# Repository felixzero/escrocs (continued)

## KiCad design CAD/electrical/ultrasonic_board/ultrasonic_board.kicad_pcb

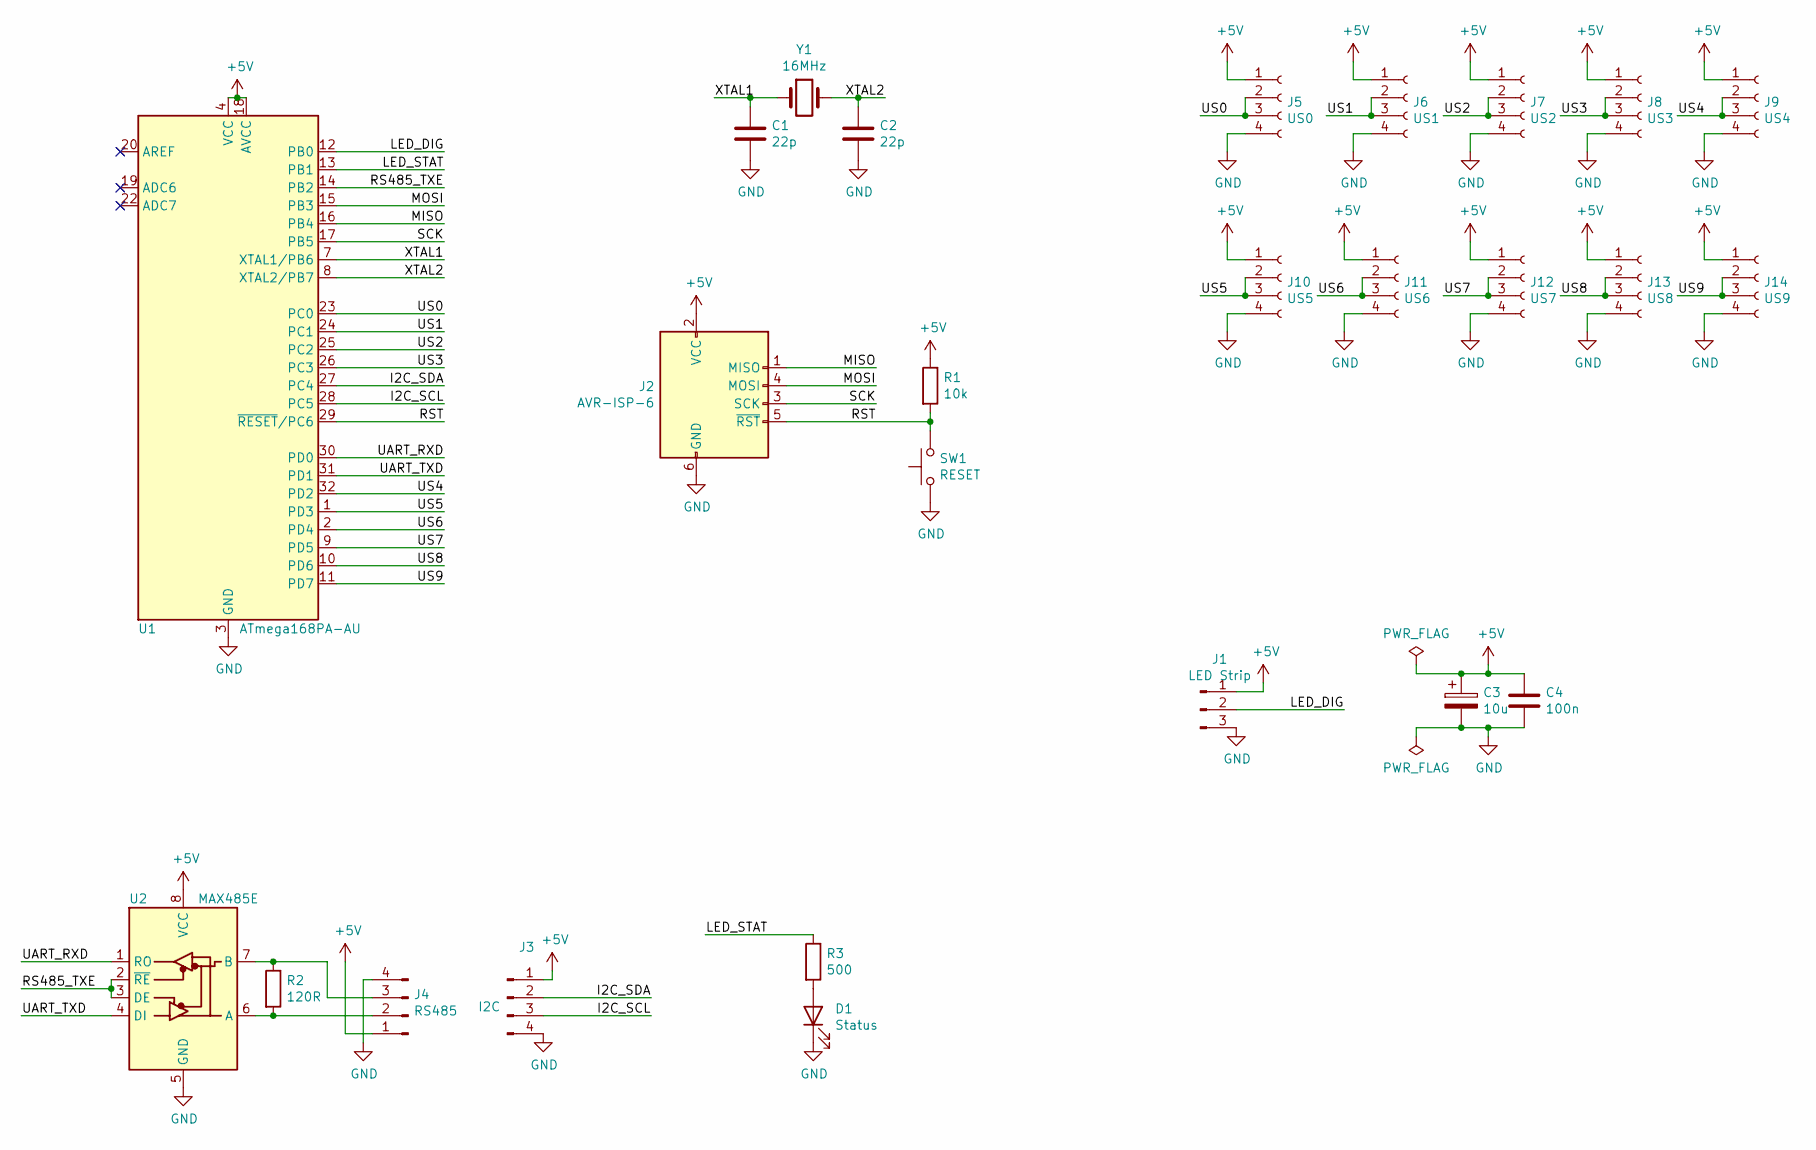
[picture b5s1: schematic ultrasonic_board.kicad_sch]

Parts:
C1, C2: 22p; C_0603_1608Metric
C3: 10u; CP_Radial_D8.0mm_P3.80mm
C4: 100n; C_0603_1608Metric
D1: Status; LED_0805_2012Metric
J1: LED Strip; Molex_KK-254_AE-6410-03A_1x03_P2.54mm_Vertical
J2: AVR-ISP-6; PinHeader_2x03_P2.54mm_Vertical
J3: I2C; Molex_KK-254_AE-6410-04A_1x04_P2.54mm_Vertical
J4: RS485; Molex_KK-254_AE-6410-04A_1x04_P2.54mm_Vertical
J5: US0; PinSocket_1x04_P2.54mm_Vertical
J6: US1; PinSocket_1x04_P2.54mm_Vertical
J7: US2; PinSocket_1x04_P2.54mm_Vertical
J8: US3; PinSocket_1x04_P2.54mm_Vertical
J9: US4; PinSocket_1x04_P2.54mm_Vertical
J10: US5; PinSocket_1x04_P2.54mm_Vertical
J11: US6; PinSocket_1x04_P2.54mm_Vertical
J12: US7; PinSocket_1x04_P2.54mm_Vertical
J13: US8; PinSocket_1x04_P2.54mm_Vertical
J14: US9; PinSocket_1x04_P2.54mm_Vertical
R1: 10k; R_0603_1608Metric
R2: 120R; R_0603_1608Metric
R3: 500; R_0603_1608Metric
SW1: RESET; SW_PUSH_6mm
U1: ATmega168PA-AU; TQFP-32_7x7mm_P0.8mm
U2: MAX485E; SOIC-8_3.9x4.9mm_P1.27mm
Y1: 16MHz; Crystal_SMD_HC49-SD

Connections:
+5V: C3.1, C4.1, J1.1, J2.2 (VCC), J3.1, J4.1, J5.1, J6.1, J7.1, J8.1, J9.1, J10.1, J11.1, J12.1, J13.1, J14.1, R1.1, U1.4 (VCC), U1.6 (VCC), U1.18 (AVCC), U2.8 (VCC)
/I2C_SCL: J3.3, U1.28 (PC5)
/I2C_SDA: J3.2, U1.27 (PC4)
/LED_DIG: J1.2, U1.12 (PB0)
/LED_STAT: R3.1, U1.13 (PB1)
/MISO: J2.1 (MISO), U1.16 (PB4)
/MOSI: J2.4 (MOSI), U1.15 (PB3)
/RS485_TXE: U1.14 (PB2), U2.2 (~RE), U2.3 (DE)
/RST: J2.5 (~RST), R1.2, SW1.2, U1.29 (~RESET/PC6)
/SCK: J2.3 (SCK), U1.17 (PB5)
/UART_RXD: U1.30 (PD0), U2.1 (RO)
/UART_TXD: U1.31 (PD1), U2.4 (DI)
/US0: J5.2, J5.3, U1.23 (PC0)
/US1: J6.2, J6.3, U1.24 (PC1)
/US2: J7.2, J7.3, U1.25 (PC2)
/US3: J8.2, J8.3, U1.26 (PC3)
/US4: J9.2, J9.3, U1.32 (PD2)
/US5: J10.2, J10.3, U1.1 (PD3)
/US6: J11.2, J11.3, U1.2 (PD4)
/US7: J12.2, J12.3, U1.9 (PD5)
/US8: J13.2, J13.3, U1.10 (PD6)
/US9: J14.2, J14.3, U1.11 (PD7)
/XTAL1: C1.1, U1.7 (XTAL1/PB6), Y1.1
/XTAL2: C2.1, U1.8 (XTAL2/PB7), Y1.2
GND: C1.2, C2.2, C3.2, C4.2, D1.1 (K), J1.3, J2.6 (GND), J3.4, J4.4, J5.4, J6.4, J7.4, J8.4, J9.4, J10.4, J11.4, J12.4, J13.4, J14.4, SW1.1, U1.3 (GND), U1.5 (GND), U1.21 (GND), U2.5 (GND)
unnamed: D1.2 (A), R3.2
unnamed: J4.2, R2.2, U2.6 (A)
unnamed: J4.3, R2.1, U2.7 (B)

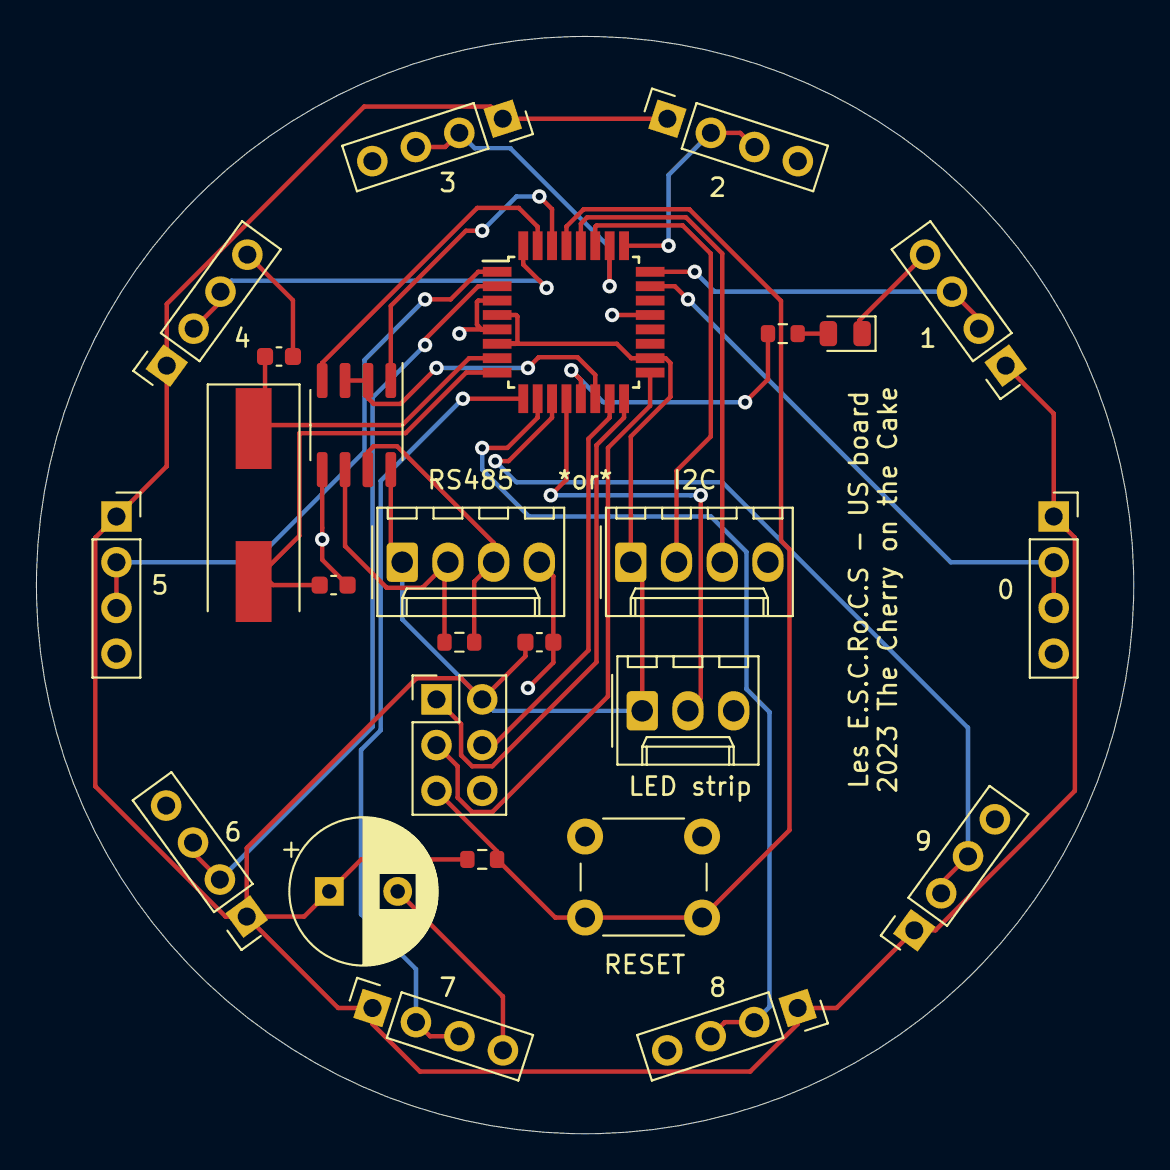
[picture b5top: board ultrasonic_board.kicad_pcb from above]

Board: 2 copper layers, 61.0 x 61.0 mm, 26 parts (0 on the bottom side), 28 nets.

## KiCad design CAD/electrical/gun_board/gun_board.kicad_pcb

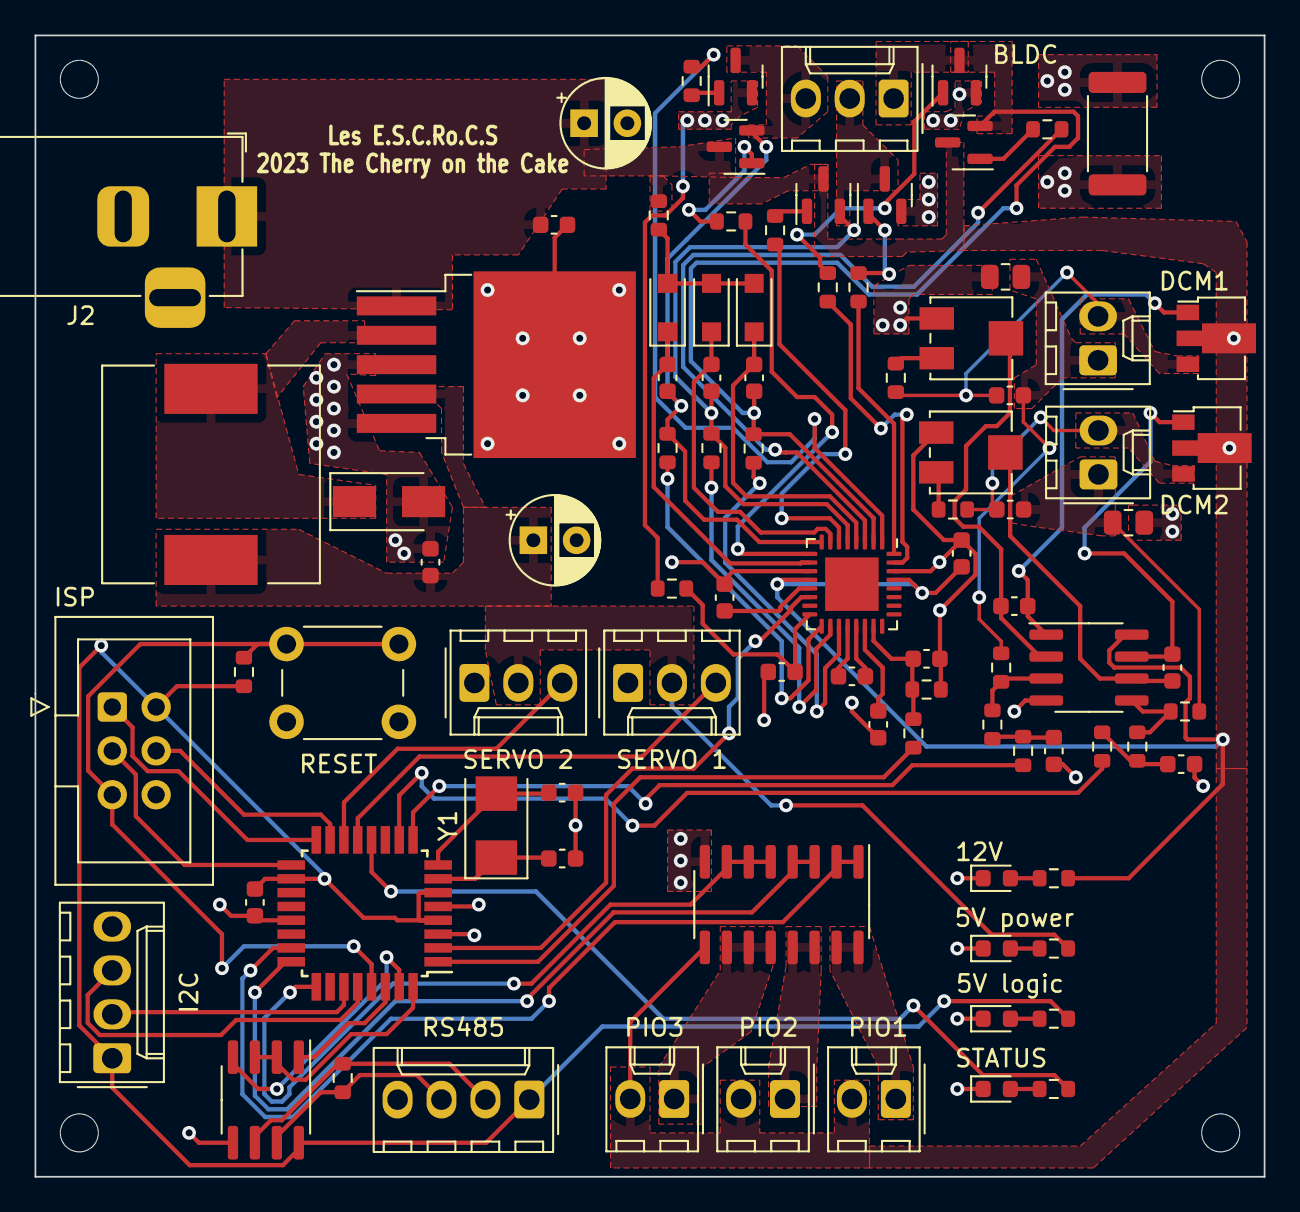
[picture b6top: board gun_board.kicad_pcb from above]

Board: 2 copper layers, 71.1 x 66.0 mm, 91 parts (0 on the bottom side), 78 nets.

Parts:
5V logic, 5V power, 12V: LED; LED_0603_1608Metric
BLDC: BLDC; Molex_KK-254_AE-6410-03A_1x03_P2.54mm_Vertical
C1, C3: 22p; C_0603_1608Metric
C2, C5, C7, C8, C11, C14, C16, C18, C19, C20, C21, C22: 100n; C_0603_1608Metric
C4: 47u; CP_Radial_D5.0mm_P2.50mm
C6: 10u; CP_Radial_D5.0mm_P2.50mm
C9, C10, C12, C13: 22n; C_0603_1608Metric
C15, C17: 100p; C_0603_1608Metric
D1: SS54; D_SMA
D6, D7, D8: D; D_SOD-123F
DCM1: DC Motor 1; Molex_KK-254_AE-6410-02A_1x02_P2.54mm_Vertical
DCM2: DC Motor 2; Molex_KK-254_AE-6410-02A_1x02_P2.54mm_Vertical
I2C: I2C; Molex_KK-254_AE-6410-04A_1x04_P2.54mm_Vertical
ISP: AVR-ISP-6; IDC-Header_2x03_P2.54mm_Vertical
J2: Barrel_Jack; BarrelJack_Horizontal
L2: 100u; L_12x12mm_H6mm
PIO1: HPIO 1; Molex_KK-254_AE-6410-02A_1x02_P2.54mm_Vertical
PIO2: HPIO 2; Molex_KK-254_AE-6410-02A_1x02_P2.54mm_Vertical
PIO3: HPIO 3; Molex_KK-254_AE-6410-02A_1x02_P2.54mm_Vertical
Q1, Q2: C9634; SOT-89-3
Q3, Q4, Q5, Q6, Q7, Q8: AO3400A; SOT-23
R1: 470R; R_0603_1608Metric
R2, R4, R5: 100R; R_0603_1608Metric
R3: 120R; R_0603_1608Metric
R6, R7, R8, R9, R10, R12, R13, R14, R15, R17, R19: 10k; R_0603_1608Metric
R11, R16: 1R; R_0805_2012Metric
R18: 100k; R_0603_1608Metric
R20: 10R; R_0603_1608Metric
R21, R22, R23, R24, R25, R26: 47R; R_0603_1608Metric
R27: 60mR; R_2512_6332Metric
R28, R29, R30: 33k; R_0603_1608Metric
RESET: RESET; SW_PUSH_6mm
RS485: RS485; Molex_KK-254_AE-6410-04A_1x04_P2.54mm_Vertical
RV1, RV2: 1k; Potentiometer_Bourns_3314J_Vertical
SERVO 1: Servo 1; Molex_KK-254_AE-6410-03A_1x03_P2.54mm_Vertical
SERVO 2: Servo 2; Molex_KK-254_AE-6410-03A_1x03_P2.54mm_Vertical
STATUS: LED; LED_0603_1608Metric
U1: LM2576HVS-5; TO-263-5_TabPin3
U2: ATmega328P-A; TQFP-32_7x7mm_P0.8mm
U3: MAX485E; SOIC-8_3.9x4.9mm_P1.27mm
U4: LM2904; SOIC-8_3.9x4.9mm_P1.27mm
U5: ULN2003; SOIC-16_3.9x9.9mm_P1.27mm
U6: PT2522; QFN-32-1EP_5x5mm_P0.5mm_EP3.1x3.1mm
Y1: Crystal; Crystal_SMD_5032-2Pin_5.0x3.2mm

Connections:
+5V: C2.1, I2C.1, ISP.2 (VCC), R4.1, R6.1, RS485.1, U2.4 (VCC), U2.6 (VCC), U2.18 (AVCC), U3.8 (VCC)
+5VP: C6.1, C7.1, L2.2, R2.1, SERVO 1.2, SERVO 2.2, U1.4 (FB)
+12V: C4.1, C5.1, C18.1, J2.1, PIO1.2, PIO2.2, PIO3.2, Q1.2 (C), Q2.2 (C), Q3.3 (D), Q5.3 (D), Q7.3 (D), R1.1, R20.1, U1.1 (VIN), U4.8 (V+), U5.9 (COM), U6.12 (VDD), U6.29 (VCC)
/BLDC driver/UO: BLDC.3, C20.2, Q3.2 (S), Q4.3 (D), R28.1, U6.8 (VS1)
/BLDC driver/VO: BLDC.2, C21.2, Q5.2 (S), Q6.3 (D), R29.1, U6.5 (VS2)
/BLDC driver/WO: BLDC.1, C22.2, Q7.2 (S), Q8.3 (D), R30.1, U6.2 (VS3)
/BLDC driver/ZCU: R28.2, U6.17 (ZCU)
/BLDC driver/ZCV: R29.2, U6.18 (ZCV)
/BLDC driver/ZCW: R30.2, U6.19 (ZCW)
/BLDC_FW: U2.2 (PD4), U6.14 (FWR)
/BLDC_PWM: R17.2, U2.1 (PD3)
/DCM1_PWM: R7.1, U2.9 (PD5)
/DCM2_PWM: R12.1, U2.10 (PD6)
/HPIO1: U2.23 (PC0), U5.1 (I1), U5.2 (I2)
/HPIO2: U2.24 (PC1), U5.3 (I3), U5.4 (I4)
/HPIO3: U2.25 (PC2), U5.5 (I5), U5.6 (I6), U5.7 (I7)
/I2C_SCL: I2C.3, U2.28 (PC5)
/I2C_SDA: I2C.2, U2.27 (PC4)
/RS485_TXE: U2.32 (PD2), U3.2 (~RE), U3.3 (DE)
/RST: ISP.5 (~RST), R6.2, RESET.1, U2.29 (~RESET/PC6)
/SERVO1: SERVO 1.3, U2.13 (PB1)
/SERVO2: SERVO 2.3, U2.14 (PB2)
/SPI_MISO: ISP.1 (MISO), U2.16 (PB4)
/SPI_MOSI: ISP.4 (MOSI), U2.15 (PB3)
/SPI_SCK: ISP.3 (SCK), U2.17 (PB5)
/STATUS: R5.1, U2.12 (PB0)
/Tunable DC Motor 1/M+: C10.1, DCM1.2, Q1.3 (E), R10.1
/Tunable DC Motor 1/M-: C10.2, DCM1.1, R9.2, R11.1
/Tunable DC Motor 2/M+: C13.1, DCM2.2, Q2.3 (E), R15.1
/Tunable DC Motor 2/M-: C13.2, DCM2.1, R14.2, R16.1
/UART_RXD: U2.30 (PD0), U3.1 (RO)
/UART_TXD: U2.31 (PD1), U3.4 (DI)
/XTAL1: C1.1, U2.7 (XTAL1/PB6), Y1.1
/XTAL2: C3.1, U2.8 (XTAL2/PB7), Y1.2
GND: 5V logic.1 (K), 5V power.1 (K), 12V.1 (K), C1.2, C2.2, C3.2, C4.2, C5.2, C6.2, C7.2, C8.2, C11.2, C14.2, C15.2, C16.2, C18.2, C19.1, D1.2 (A), I2C.4, ISP.6 (GND), J2.2, R11.2, R16.2, R18.2, R27.2, RESET.2, RS485.4, RV1.1, RV2.1, SERVO 1.1, SERVO 2.1, STATUS.1 (K), U1.3 (GND), U1.5 (~ON/OFF), U2.3 (GND), U2.5 (GND), U2.21 (GND), U3.5 (GND), U4.4 (V-), U5.8 (GND), U6.11 (GND), U6.30 (VSS)
unnamed: C8.1, R7.2, R8.1
unnamed: C9.1, Q1.1 (B), U4.1
unnamed: C9.2, RV1.2, U4.2 (-)
unnamed: C11.1, R12.2, R13.1
unnamed: C12.1, Q2.1 (B), U4.7
unnamed: C12.2, RV2.2, U4.6 (-)
unnamed: C14.1, R17.1, R18.1, U6.23 (VSP)
unnamed: C15.1, U6.22 (OSC)
unnamed: C16.1, R19.2, U6.16 (RF)
unnamed: C17.1, U6.20 (COM)
unnamed: C17.2, U6.21 (FLT)
unnamed: C19.2, U6.13 (VREG)
unnamed: C20.1, D6.1 (K), U6.10 (VB1)
unnamed: C21.1, D7.1 (K), U6.7 (VB2)
unnamed: C22.1, D8.1 (K), U6.4 (VB3)
unnamed: D1.1 (K), L2.1, U1.2 (OUT)
unnamed: 12V.2 (A), R1.2
unnamed: 5V power.2 (A), R2.2
unnamed: 5V logic.2 (A), R4.2
unnamed: R5.2, STATUS.2 (A)
unnamed: D6.2 (A), D7.2 (A), D8.2 (A), R20.2
unnamed: R3.2, RS485.2, U3.6 (A)
unnamed: R3.1, RS485.3, U3.7 (B)
unnamed: PIO1.1, U5.15 (O2), U5.16 (O1)
unnamed: PIO2.1, U5.13 (O4), U5.14 (O3)
unnamed: PIO3.1, U5.10 (O7), U5.11 (O6), U5.12 (O5)
unnamed: Q3.1 (G), R21.2
unnamed: Q4.1 (G), R26.2
unnamed: Q4.2 (S), Q6.2 (S), Q8.2 (S), R19.1, R27.1
unnamed: Q5.1 (G), R22.2
unnamed: Q6.1 (G), R23.2
unnamed: Q7.1 (G), R24.2
unnamed: Q8.1 (G), R25.2
unnamed: R8.2, R9.1, U4.3 (+)
unnamed: R10.2, RV1.3
unnamed: R13.2, R14.1, U4.5 (+)
unnamed: R15.2, RV2.3
unnamed: R21.1, U6.9 (HO1)
unnamed: R22.1, U6.6 (HO2)
unnamed: R23.1, U6.32 (LO2)
unnamed: R24.1, U6.3 (HO3)
unnamed: R25.1, U6.31 (LO3)
unnamed: R26.1, U6.1 (LO1)

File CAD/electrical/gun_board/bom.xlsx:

Comment | Designator | Footprint | LCSC Part Number
22pF capacitor | C1,C3 | 0603 | C1653
100nF capacitor | C2,C5,C7,C8,C11,C14,C16,C18,C19,C20,C21,C22 | 0603 | C14663
22nF capacitor | C9,C10,C12,C13 | 0603 | C21122
100pF capacitor | C15,C17 | 0603 | C14858
SS54 diode | D1 | SMA | C22452
LED | D2,D3,D4,D5 | 0603 | C72038
Diode | D6,D7,D8 | SOD-123F | C64898
100µH inductor | L2 | 12x12 | C169378
C9634 NPN | Q1,Q2 | SOT-89-3 | C9634
AO3400 n-channel mosfet | Q3,Q4,Q5,Q6,Q7,Q8 | SOT-23 | C20917
470r resistor | R1 | 0603 | C23179
100r resistor | R2,R4,R5 | 0603 | C22775
120r resistor | R3 | 0603 | C22787
10k resistor | R6,R7,R8,R9,R10,R12,R13,R14,R15,R17,R19 | 0603 | C25804
1r resistor | R11,R16 | 0805 | C25271
100k resistor | R18 | 0603 | C25803
47r resistor | R21,R22,R23,R24,R25,R26 | 0603 | C23182
60mr resistor (sense) | R27 | 2512 | C87222
33k resistor | R28,R29,R30 | 0603 | C4216
1k potentiometer | RV1,RV2 | Bourns 3314J | C124640
LM2576 | U1 | TO-263-5 | C34465
ATmega328P or 168pa-au | U2 | TQFP-32 | C14877
MAX485 | U3 | SOIC-8 | C19738
LM2904 or LM358 or LM393 | U4 | SOIC-8 | C7955
ULN2003 | U5 | SOIC-16 | C7512
PT2522 | U6 | QFN-32-1EP | C481965
8MHz crystal | Y1 | 5032 | C115962

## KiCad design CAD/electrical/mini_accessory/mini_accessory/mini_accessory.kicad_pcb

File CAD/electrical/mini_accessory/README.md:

# Mini accessory board

A smaller version of the accessory board with only servos. It did not arrived in time for the 2022 cup (thanks German customs...)

## Known issues

Untested, no firmware written.

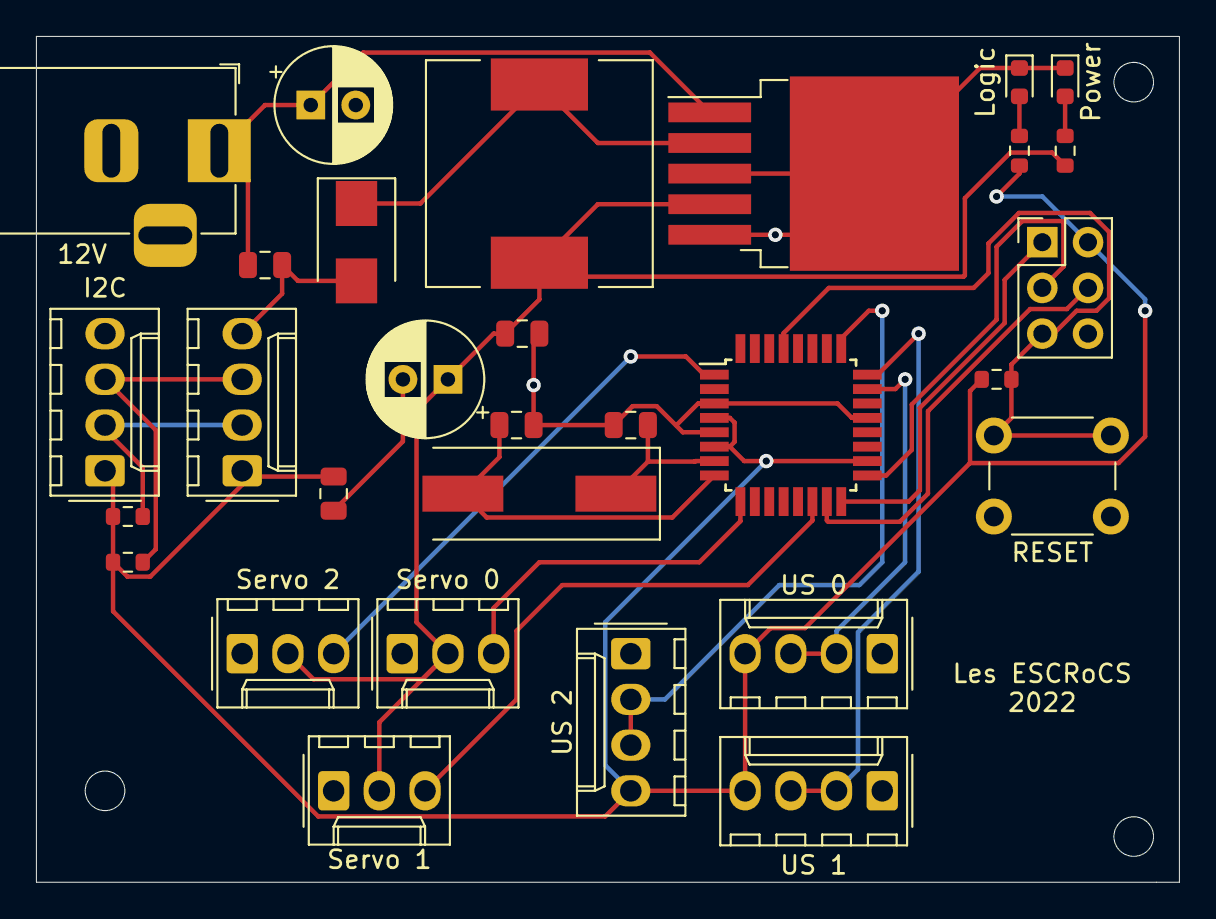
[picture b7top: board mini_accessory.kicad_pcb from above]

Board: 2 copper layers, 63.5 x 47.0 mm, 30 parts (0 on the bottom side), 21 nets.

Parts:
12V: 12V in; BarrelJack_Horizontal
C1, C3: 10u; CP_Radial_D6.3mm_P2.50mm
C2, C4, C7: 100n; C_0805_2012Metric
C5, C6: 22p; C_0805_2012Metric
D3: SS54; D_SMB
I2C: I2C; Molex_KK-254_AE-6410-04A_1x04_P2.54mm_Vertical
J3: AVR-ISP-6; PinHeader_2x03_P2.54mm_Vertical
J4: I2C; Molex_KK-254_AE-6410-04A_1x04_P2.54mm_Vertical
L1: 10u; L_12x12mm_H6mm
Logic: 5V; LED_0603_1608Metric
Power: 5VP; LED_0603_1608Metric
R1, R2: 470; R_0603_1608Metric
R3, R4, R5: 10k; R_0603_1608Metric
RESET: Reset; SW_PUSH_6mm
Servo 0: Servo 0; Molex_KK-254_AE-6410-03A_1x03_P2.54mm_Vertical
Servo 1: Servo 1; Molex_KK-254_AE-6410-03A_1x03_P2.54mm_Vertical
Servo 2: Servo 2; Molex_KK-254_AE-6410-03A_1x03_P2.54mm_Vertical
U1: LM2576HVS-5; TO-263-5_TabPin3
U2: ATmega168PA-AU; TQFP-32_7x7mm_P0.8mm
US 0: Ultrasound 0; Molex_KK-254_AE-6410-04A_1x04_P2.54mm_Vertical
US 1: Ultrasound 1; Molex_KK-254_AE-6410-04A_1x04_P2.54mm_Vertical
US 2: Ultrasound 2; Molex_KK-254_AE-6410-04A_1x04_P2.54mm_Vertical
Y1: 16MHz; Crystal_SMD_HC49-SD

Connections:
+5V: C7.1, I2C.1, J3.2, J4.1, R1.1, R3.1, R4.1, R5.1, U2.4, U2.6, U2.18, US 0.4, US 1.4, US 2.4
+5VP: C3.1, C4.1, L1.2, R2.1, Servo 0.2, Servo 1.2, Servo 2.2, U1.4
/MISO: J3.1, U2.16
/MOSI: J3.4, U2.15
/RST: J3.5, R4.2, RESET.2, U2.29
/SCK: J3.3, U2.17
/SCL: I2C.3, J4.3, R5.2
/SDA: I2C.2, J4.2, R3.2
/SERVO0: Servo 0.3, U2.9
/SERVO1: Servo 1.3, U2.14
/SERVO2: Servo 2.3, U2.1
/US0: U2.23, US 0.2, US 0.3
/US1: U2.24, US 1.2, US 1.3
/US2: U2.25, US 2.2, US 2.3
/XTAL1: C5.1, U2.7, Y1.1
/XTAL2: C6.1, U2.8, Y1.2
GND: 12V.2, C1.2, C2.2, C3.2, C4.2, C5.2, C6.2, C7.2, D3.2, I2C.4, J3.6, J4.4, Logic.1, Power.1, RESET.1, Servo 0.1, Servo 1.1, Servo 2.1, U1.3, U1.5, U2.3, U2.5, U2.21, US 0.1, US 1.1, US 2.1
unnamed: 12V.1, C1.1, C2.1, U1.1
unnamed: Logic.2, R1.2
unnamed: Power.2, R2.2
unnamed: D3.1, L1.1, U1.2

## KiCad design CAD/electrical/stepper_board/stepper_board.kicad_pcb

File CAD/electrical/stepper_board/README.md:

# Stepper board

A board, based on an ATMega168PA, meant to control up to 3 1.5A bipolar steppers (the most common kind, used in 3D printers for instance). It can also control up to 3 12V pumps.

Its code is in the `code/stepper_board` folder.

## Known issues

The steppers stay actively driven all the time. Over prolonged use of time, the card can get really hot, we recommend to use heatsinks on the stepper drivers.

A workaround to permit the microcontroller to switch off the drivers is the set the fuse in such a way that the RESET pin is a regular I/O of the ATMega and let the ATMega hold RESET down when the steppers are not in use. Beware: doing so will prevent reflashing the board.

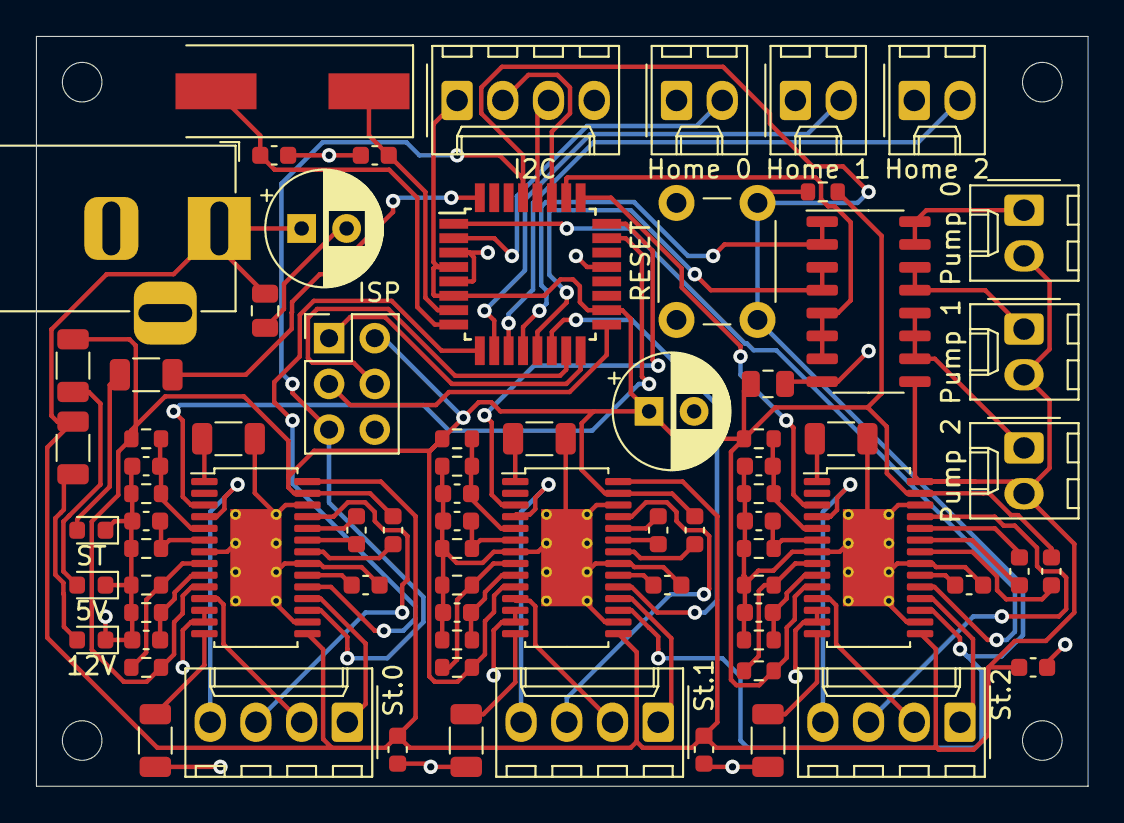
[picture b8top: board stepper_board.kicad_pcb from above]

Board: 2 copper layers, 58.4 x 41.7 mm, 77 parts (0 on the bottom side), 72 nets.

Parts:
5V: 5V; LED_0603_1608Metric
12V: 12V; LED_0603_1608Metric
C1, C7, C13, C15, C17, C25: 100n; C_0603_1608Metric
C2, C3, C8, C9, C26, C27: 1n; C_0603_1608Metric
C4, C5, C6, C10, C11, C12, C28, C29, C30: 220n; C_0603_1608Metric
C14, C18: 10u; CP_Radial_D6.3mm_P2.50mm
C16, C19: 100n; C_0805_2012Metric
C20, C24: 22p; C_0603_1608Metric
Home 0: Home 0; Molex_KK-254_AE-6410-02A_1x02_P2.54mm_Vertical
Home 1: Home 1; Molex_KK-254_AE-6410-02A_1x02_P2.54mm_Vertical
Home 2: Home 2; Molex_KK-254_AE-6410-02A_1x02_P2.54mm_Vertical
I2C: I2C; Molex_KK-254_AE-6410-04A_1x04_P2.54mm_Vertical
ISP: ISP; PinHeader_2x03_P2.54mm_Vertical
J3: 12V; BarrelJack_Horizontal
Pump 0: Pump 0; Molex_KK-254_AE-6410-02A_1x02_P2.54mm_Vertical
Pump 1: Pump 1; Molex_KK-254_AE-6410-02A_1x02_P2.54mm_Vertical
Pump 2: Pump 2; Molex_KK-254_AE-6410-02A_1x02_P2.54mm_Vertical
R1, R4, R9, R12, R29, R32: 47k; R_0603_1608Metric
R2, R3, R6, R10, R11, R14, R28, R30, R31, R34: 10k; R_0603_1608Metric
R5, R13, R33: 33k; R_0603_1608Metric
R7, R8, R15, R16, R35, R36: 0.1; R_1206_3216Metric
R25, R26, R27: 470; R_1206_3216Metric
RESET: RESET; SW_PUSH_6mm
ST: ST; LED_0603_1608Metric
St.0, St.1, St.2: Stepper; Molex_KK-254_AE-6410-04A_1x04_P2.54mm_Vertical
U1: ATmega168PA-AU; TQFP-32_7x7mm_P0.8mm
U2, U4, U5: DRV8811; HTSSOP-28-1EP_4.4x9.7mm_P0.65mm_EP2.85x5.4mm_ThermalVias
U3: ULN2003; SO-16_3.9x9.9mm_P1.27mm
Y1: Crystal; Crystal_SMD_HC49-SD

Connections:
+5V: C5.1, C11.1, C14.1, C16.1, C29.1, I2C.1, ISP.2, R2.1, R5.1, R10.1, R13.1, R26.1, R28.1, R30.1, R33.1, U1.4, U1.6, U1.18, U2.10, U2.27, U4.10, U4.27, U5.10, U5.27
+12V: C13.1, C15.1, C17.1, C18.1, C19.1, J3.1, Pump 0.2, Pump 1.2, Pump 2.2, R27.1, U2.15, U2.28, U3.9, U4.15, U4.28, U5.15, U5.28
/DIR0: U1.23, U2.3
/DIR1: U1.24, U4.3
/DIR2: U1.25, U5.3
/HOME0: Home 0.2, U1.2
/HOME1: Home 1.2, U1.10
/HOME2: Home 2.2, U1.11
/I2C_SCL: I2C.3, U1.28
/I2C_SDA: I2C.2, U1.27
/PUMP0: U1.12, U3.1, U3.2
/PUMP1: U1.13, U3.3, U3.4
/PUMP2: U1.26, U3.5, U3.6, U3.7
/RST: ISP.5, R28.2, RESET.2, U1.29, U2.17, U4.17, U5.17
/SPI_MISO: ISP.1, U1.16
/SPI_MOSI: ISP.4, U1.15
/SPI_SCK: ISP.3, U1.17
/STATUS: R25.1, U1.32
/STEP0: U1.9, U2.19
/STEP1: U1.14, U4.19
/STEP2: U1.1, U5.19
/XTAL1: C20.1, U1.7, Y1.1
/XTAL2: C24.1, U1.8, Y1.2
GND: 5V.1, 12V.1, C1.2, C2.2, C3.2, C6.1, C7.2, C8.2, C9.2, C12.1, C13.2, C14.2, C15.2, C16.2, C17.2, C18.2, C19.2, C20.2, C24.2, C25.2, C26.2, C27.2, C30.1, Home 0.1, Home 1.1, Home 2.1, I2C.4, ISP.6, J3.2, R1.2, R3.2, R4.2, R6.2, R7.2, R8.2, R9.2, R11.2, R12.2, R14.2, R15.2, R16.2, R29.2, R31.2, R32.2, R34.2, R35.2, R36.2, RESET.1, ST.1, U1.3, U1.5, U1.21, U2.7, U2.12, U2.13, U2.16, U2.21, U2.26, U2.29, U3.8, U4.7, U4.12, U4.13, U4.16, U4.21, U4.26, U4.29, U5.7, U5.12, U5.13, U5.16, U5.21, U5.26, U5.29
unnamed: C1.1, R2.2, R3.1, U4.5
unnamed: C2.1, R1.1, U4.6
unnamed: C3.1, R4.1, U4.9
unnamed: C4.1, U4.23
unnamed: C4.2, U4.24
unnamed: C5.2, U4.22
unnamed: C6.2, U4.20
unnamed: C7.1, R10.2, R11.1, U5.5
unnamed: C8.1, R9.1, U5.6
unnamed: C9.1, R12.1, U5.9
unnamed: C10.1, U5.23
unnamed: C10.2, U5.24
unnamed: C11.2, U5.22
unnamed: C12.2, U5.20
unnamed: C25.1, R30.2, R31.1, U2.5
unnamed: C26.1, R29.1, U2.6
unnamed: C27.1, R32.1, U2.9
unnamed: C28.1, U2.23
unnamed: C28.2, U2.24
unnamed: C29.2, U2.22
unnamed: C30.2, U2.20
unnamed: R25.2, ST.2
unnamed: 5V.2, R26.2
unnamed: 12V.2, R27.2
unnamed: St.1.1, U4.18
unnamed: St.1.2, U4.11
unnamed: St.1.3, U4.25
unnamed: St.1.4, U4.4
unnamed: St.2.1, U5.18
unnamed: St.2.2, U5.11
unnamed: St.2.3, U5.25
unnamed: St.2.4, U5.4
unnamed: Pump 0.1, U3.15, U3.16
unnamed: Pump 1.1, U3.13, U3.14
unnamed: Pump 2.1, U3.10, U3.11, U3.12
unnamed: St.0.1, U2.18
unnamed: St.0.2, U2.11
unnamed: St.0.3, U2.25
unnamed: St.0.4, U2.4
unnamed: R5.2, R6.1, U4.8
unnamed: R7.1, U4.1
unnamed: R8.1, U4.14
unnamed: R13.2, R14.1, U5.8
unnamed: R15.1, U5.1
unnamed: R16.1, U5.14
unnamed: R33.2, R34.1, U2.8
unnamed: R35.1, U2.1
unnamed: R36.1, U2.14

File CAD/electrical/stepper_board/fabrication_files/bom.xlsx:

Comment | Designator | Footprint | LCSC Part Number
100n | C16,C19 | Capacitor_SMD:C_0805_2012Metric | C28233
22p | C20,C24 | Capacitor_SMD:C_0603_1608Metric | C1653
100n | C1,C7,C13,C15,C17,C25 | Capacitor_SMD:C_0603_1608Metric | C14663
1n | C2,C3,C8,C9,C26,C27 | Capacitor_SMD:C_0603_1608Metric | C1588
220n | C4,C5,C6,C10,C11,C12,C28,C29,C30 | Capacitor_SMD:C_0603_1608Metric | C21120
Status LED | D1,D2,D3 | LED_SMD:LED_0603_1608Metric | C72038
300o | R25,R26,R27 | Resistor_SMD:R_1206_3216Metric | C17887
10k | R2,R3,R6,R10,R11,R14,R28,R30,R31,R34 | Resistor_SMD:R_0603_1608Metric | C25804
47k | R1,R4,R9,R12,R29,R32 | Resistor_SMD:R_0603_1608Metric | C25819
33k | R5,R13,R33 | Resistor_SMD:R_0603_1608Metric | C4216
0.1 | R7,R8,R15,R16,R35,R36 | Resistor_SMD:R_1206_3216Metric | C25334
ATmega168PA-AU | U1 | Package_QFP:TQFP-32_7x7mm_P0.8mm | C8728
DRV8811 | U2,U4,U5 | Package_SO:HTSSOP-28-1EP_4.4x9.7mm_P0.65mm_EP2.85x5.4mm_ThermalVias | C133174
ULN2003 | U3 | Package_SO:SO-16_3.9x9.9mm_P1.27mm | C7512
Crystal | Y1 | Crystal:Crystal_SMD_HC49-SD | C12674

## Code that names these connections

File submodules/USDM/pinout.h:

#pragma once

/* Those are covered by PCINT2 */
//#define PIN_SERIAL_RX    0
//#define PIN_SERIAL_TX    1
/* Standard US module */
#define PIN_ECHO_1       2
#define PIN_ECHO_2       3
#define PIN_ECHO_3       4
#define PIN_ECHO_4       5
#define PIN_ECHO_5       6
#define PIN_ECHO_6       7

/* Thoses are covered by PCINT0 */
#define PIN_SWITCH   8
#define LED_PIN  9 //Neopixel ring command
/*#define PIN_SERVOS_BLANK 9
#define PIN_SPI_SS       10
#define PIN_SPI_MOSI     11
#define PIN_SPI_MISO     12
#define PIN_SPI_SCK      13*/

/* Those are covered by PCINT1 */
//#define PIN_NC          A0
//#define PIN_NC          A1
//#define PIN_NC          A2
/*#define PIN_STARTER     A3
#define PIN_I2C_SDA     A4
#define PIN_I2C_SCL     A5*/

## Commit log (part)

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2019-10-27 Initial code for Arduino.
2019-12-01 Sensors & Actuators
    Code de test unitaires des sous-systèmes:
    - Module Sonar HC-SR04 x2
    - Micro Servo Tower 9g
2020-01-22 Add RF submodule.
2020-01-22 Add forgotten parameters for RX. Oops.
2020-01-24 Add CAD design files to git.
2020-01-29 Add mast and top plate designs.
2020-01-30 Add code for magnetometer.
2020-01-31 Add CAD design for antenna.
2020-01-31 Remove duplicate mangetometer folder.
2020-02-06 Add flag, top plate design and move Servo to its own folder.
2020-02-09 Reorganise the code in main code and submodules.
2020-02-18 Add several cards & parts.
2020-02-20 Reformat code into a C++ object interface. Make servo module work.
2020-02-21 Fix servo board code.
2020-02-21 Add servo board CAD design.
2020-02-21 Always test before comitting!!!
2020-02-23 Add some mechanical parts.
2020-03-12 Make servo board work fine.
2020-03-14 Fix servo code
2020-03-18 Start routine for robot
2020-03-19 Robot homologué !
2020-10-14 Add ecueil
2020-10-25 Implementing first real strategy
2020-10-26 Add windsock routine
2020-10-26 debugging
2020-10-27 Ready for the cup!?
2020-10-28 Robot homologué
2020-10-28 42 or 47 points
2020-10-28 44 ou 49 points
2020-10-30 On a fait 64 points avec ça
2020-11-02 Nouveau design de carte servo
2020-11-02 Remove antenna board (useless)
2020-11-02 New power supply card and lighthouse card
2020-11-12 Electronics sent to manufacturer
2020-11-12 First version of trigger
2020-11-22 Add score board and LCD control code
2021-01-02 Ajoute la pince à gobelets
2021-01-08 Add motor control board design
2021-01-08 Add prototype patin
2021-01-08 Remove temporary files
2021-01-08 Lower wheel
2021-03-05 pince, carte elec moteur, code carte moteur
2021-06-06 CAD - Sonar holders
2021-06-20 Ajout du code de gestion de l'I2C sur la carte moteur esclave
2021-06-20 Ajout du déclencheur
2021-06-30 Ajout du mat de détection
2021-07-04 Updated pinout with triple sonar pins
2021-07-04 Triple ultrasound module
2021-07-04 Omnibot [WiP]
2021-07-06 Ready for the show!
2021-07-07 Augmentation de la vitesse
2021-07-08 This wins 57/43pts
2021-07-09 Omnibot 2021 - Homologué
    Code de la carte "moteur" du robot 2 (CdFR 2021)
2021-07-09 Omnibot US module
    Tentatives de faire fonctionner le mât ultrason
2021-07-09 Omnibot - Windsock Killer program code
    Habemus deux robots.
2021-07-29 Dernier match joué en 2021
2021-07-31 Added new US Detection module
    First commit - code still WIP
    6 US modules piloted by Arduino Nano
    Feedback via WS2812B LED ring
    Controlled via I2C
    Several modes:
    - Startup: US module check up
2021-09-04 Wind info detector
    Basic tri-state reader for getting wind orientation from raspberry layer.
    Basic implementation: Uses two digital input pins.
2021-09-07 Add code for motor board of secondary robot
2021-09-08 Motor PWM control with double buffering
2021-09-09 Add P feedback
2021-09-11 Add schematics for hacked main board and add I2C to motor board
2021-09-12 Add north/south detection and I2C control of motor board
2021-09-22 Make robot 2 roll!
2021-10-03 Add OTA and Wifi to main board
2021-10-03 Add CAD for main and accessory boards
2021-10-03 Configure ESP32 as AP
2021-10-16 Add gyroscope
2021-10-17 ArUco 2022
    ArUco tags for "Samples" game elements
    Basic python code with OpenCV for detection and color classification
2021-10-28 Add main robot support
2021-11-01 First measurements from lidar board.
2021-11-15 Add lidar board and motor board v2
2021-11-15 Add basic motor control
2021-11-21 Basic differential drive control
2021-11-22 Add acceleration control
2021-11-22 Sort everything out
2022-01-13 Lidar board v2 and stepper board
2022-01-13 Code for motor board v2 and stepper board
2022-01-13 Initial working code for lidar board
2022-02-14 Update code for lidar board
2022-02-14 Fix SSE event bug
2022-02-14 Separate differential drive and holonomic
2022-02-17 The robot rolls again!
2022-02-19 Refactor motion control code
2022-02-24 Add lua strategy player
2022-02-24 Update pump bracket
2022-02-24 Update fuse settings
2022-02-24 Add overwrite for steppers
2022-02-25 Simplify game actions
2022-02-26 Fix asserv of holonomic robot
2022-04-14 Fully working lidar board code
2022-04-24 Poster 2022
2022-05-01 Table template for 2022 Edition
2022-05-09 Fix stepper board code
2022-05-09 Add working lidar board communication
2022-05-09 Update mechanical CAD
2022-05-09 Add mini accessory board
2022-05-09 Update motor board makefile
2022-05-09 Fix stepper board - main board communication
2022-05-11 Square robot now rolls... again
2022-05-11 Add GPIO and pose overwrite
2022-05-13 Évitement !
2022-05-15 Add side change and fix holonomic robot
2022-05-15 Fix motion of robot 1
2022-05-18 Code Vitrine 2022 - trigger by contact switch, without US
2022-05-18 Add first initial strategy
2022-05-18 Add management of trigger and 100s timer
2022-05-18 Add mat de balise
2022-05-19 Add UDP logger
2022-05-19 Debug angles of holonomic and add logging
2022-05-19 Use wifi instead of I2C for lidar board
2022-05-19 Correct library for Servo + Neopixel use
2022-05-19 Basic strategy for Danzinmusay
2022-05-20 Python GUI for basic OTA control - Get, overwrite and set position (angle input is in degrees, converted to radians in the HTTP request) - Move steppers
2022-05-23 CAO statuette & pince
2022-05-23 Many importants fixes: - detection on robot triangle - lidar-main board communication - UDP logger - both strategies
2022-05-23 Support carte lidar
2022-05-23 Fix some bugs to make the robots ready for the cup.
2022-05-24 Fix asserv robot 1
2022-05-26 This can do 70
2022-05-29 Final strategy (96 points) - this landed us to 1/8th
2022-05-30 Document and clean the PCB folder
2022-05-30 Create LICENSE
2022-05-30 Vitrine triggered by ultrasonic detection
2023-03-11 Add code for ultrasonic mast
2023-03-11 Add CAD of ultrasonic board
2023-03-11 Misc stuff
2023-05-17 Update ESP32 firmware for new version
2023-05-17 Disable light display on ultrasonic mast
2023-05-17 Add ultrasonic detection on main board
2023-05-17 Fix I2C timeout issues on US board
2023-05-18 Terrain model for 2023
2023-05-18 PyCommandOTA - Pump management
    Pump Over The Air
2023-05-20 Ceci a joué en match 2023
2023-05-22 All the missing stuff that was supposed to be commited before the cup
2023-06-20 Migrate electronic projects to Kicad 6
2023-06-20 Add new base roulante \o/
2023-06-20 First implementation of LCD screen, rotary encoder and buzzer
2023-06-24 Add path blocked game action
2023-06-25 Add interface to ultrasounds in lua code
2023-07-08 Cleaning backup files
2023-07-08 [WIP] Main board V2
2023-07-08 Remove unnecessary logging
2023-07-08 [WIP] Implement RS485 in ultrasonic board
2023-07-21 Updated version of motor board and main board
2023-07-21 Updated version of motor board and main board (#3)
    * Cleaning backup files
    * [WIP] Main board V2
    * [WIP] Implement RS485 in ultrasonic board
    * Updated version of motor board and main board
2023-10-18 Add joystick control
2023-10-23 First version of code for motor board v3 (stepper) handling arbitrary ramps
2023-11-04 Add Modbus capabilities between main board, motor board and ultrasonic board
2023-11-04 Update code for main board for stepper robot (not usable as is)
2023-11-17 Code for working robot 3 rolling base
2023-11-17 Several bugfixes on main board
2023-11-19 Now with screen and menus and such
2023-11-19 Kicad CAD for mainboard and motorboard (final)
2023-11-19 Fix shebang for PyCommandOTA
2023-11-28 Fix integration of ultrasonic board
2024-01-06 Latest updates on rolling base
2024-01-10 Add initialization for peripherals
2024-01-11 Adding skeleton_coroutine in lua
2024-01-15 adding US_control, unworking stop while motion, untested strategy
2024-01-15 Add US high level processing & working US_controller
2024-01-16 Correcting issue, needing to set twice the pose to move after stop
2024-04-05 stack overflow solve
2024-04-11 overflow prevention
2024-04-21 Quick cleanup
2024-04-21 Cleanup of CAD files
2024-04-21 Lua functions improvements : Coroutines, US game_action support (#5)
    * Adding skeleton_coroutine in lua
    * table side sent to lua init, stupid line following lua
    * adding US_control, unworking stop while motion, untested strategy
    * Add US high level processing & working US_controller
    * Correcting issue, needing to set twice the pose to move after stop
    * stack overflow solve
2024-04-22 Fixing transform errors in rolling base
2024-04-22 Fix issues with Lua strategy
2024-04-27 Fix base roulante
2024-04-28 Fix strategy crashes
2024-05-01 Stratégie qui marche un peu et ralentissement du robot
2024-05-02 Fix bug where robots makes random stuff.
2024-05-02 Fix bug where robots makes random stuff. (#6)
2024-05-02 Remove non compiling files and fix race condition in US controller
2024-05-02 Remove non compiling files and fix race condition in US controller (#7)
2024-05-04 adding stupid.strat.lua
2024-05-04 Switch back from RS485 to I2C to robustify
2024-05-04 Remove platformio change
2024-05-04 Go back from RS485 to I2C
    * Remove non compiling files and fix race condition in US controller
    * Switch back from RS485 to I2C to robustify
    * Remove platformio change
2024-05-04 adding reverse strat
2024-05-04 reverse strat
2024-05-05 Make obstacle avoidance refuse obstacles outside of the terrain (#11)
2024-05-06 update strat after repas poulet
2024-05-06 Motor board back to RS485 (but with I2C on us)
2024-05-06 Lastminute (#13)
    * Make obstacle avoidance refuse obstacles outside of the terrain
    * Motor board back to RS485 (but with I2C on us)
2024-05-08 Last minute fixes
2024-05-08 Adjust parameters
2024-05-08 Adjust parameters (#14)
2024-05-10 Ceci plante mais est une base reglo
2024-05-10 Set wifi enable/disable and upgrade ESP-IDF
2024-05-12 This played the cup (poorly...)
2024-05-12 Failed competition
    * Adjust parameters
    * Ceci plante mais est une base reglo
    * Set wifi enable/disable and upgrade ESP-IDF
    * This played the cup (poorly...)
2024-06-06 adding stupid.strat, adding some safeguard & global
2024-06-16 initial_to_test_on_robot
2024-06-16 adding max_speed game_action
2024-06-22 small fix
2024-07-26 initial loca_lidar
2024-08-30 basic lidar with enac data only initial i2c (untested)
2024-09-13 updated lidar driver with intensity(/quality in code)
2024-09-22 last push
2024-10-09 commit switch PC
2024-10-18 seems to be working uart reader for esp32
2024-10-22 rearangeemnt unworking
2024-10-22 fixed amalgame (too many point overflow), desktop working, board untested
2024-11-17 latest push loca lidar almost working (check math forumula)
2024-11-20 math fix _ basic localization seems to work
2024-11-20 add to last
2024-11-25 micro_update before breaking triangle mode
2024-12-07 unworking _ before rework correspondance
2025-01-09 init branch
2025-01-18 Motor board working, motion control is not working
2025-01-25 feature(motor)Readded differential drive, holonomic unworking, with future change possible
2025-01-26 before rework matchs algorithm (unworking)
2025-01-31 Work good, need to reduce amalgame minimum pt
2025-02-02 bump
2025-02-20 clean_up strat, working robot with banderoel
2025-02-27 push cur progress
2025-03-01 push basic collision handler (untested) and disabling OTA
2025-03-02 add lidar board
2025-03-05 Lidar working on ESP (but no I2C)
2025-03-05 add ignore
2025-03-06 transitioning to new I2C API
2025-03-06 unworking, before reverting to basic
2025-03-07 before reverting to I2C V1
2025-03-07 currently rewriting to V1
2025-03-07 rework to be minimalistic
2025-03-07 I2C working
2025-03-07 micro main change
2025-03-08 sync LD06 board
2025-03-08 update PCB
2025-03-10 LD06 board colplet
2025-03-10 adding avoidance code with lidar
2025-04-16 Adding collision handling, not perfectly working yet
2025-04-16 small update on collision handler and I2C
2025-04-17 fixed evitement, tentative bouton stepper
2025-04-17 update ld06 I2C for button
2025-04-18 before reverting to I2C 1.0
2025-04-18 beggining new driver
2025-04-19 adding code à la coupe - J1
2025-04-21 code belge
2025-04-30 commit update
2025-05-26 Before refactor normal to include button
2025-05-26 last bump before coupe at home
